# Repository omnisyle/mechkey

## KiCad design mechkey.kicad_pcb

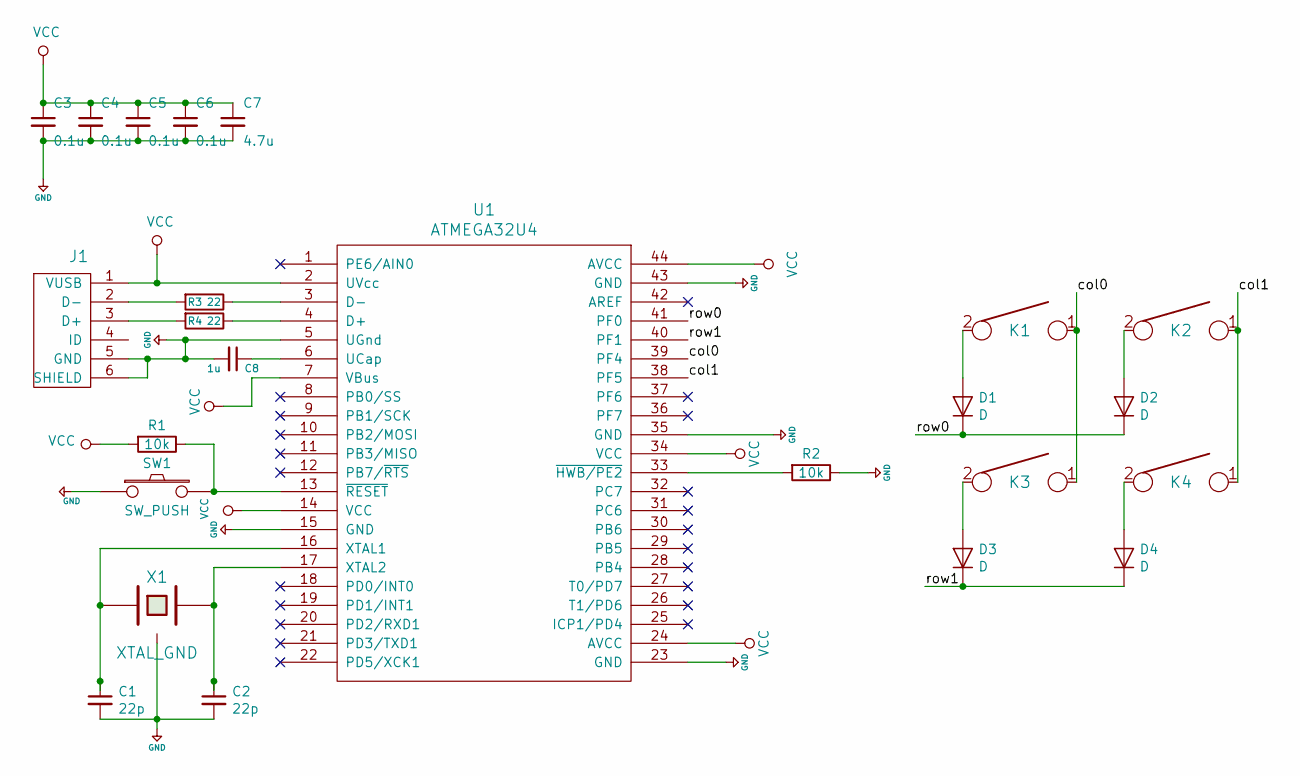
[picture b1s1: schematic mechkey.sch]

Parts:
C1, C2: 22p; C_0805_2012Metric_Pad1.15x1.40mm_HandSolder
C3, C4, C5, C6: 0.1u; C_0805_2012Metric_Pad1.15x1.40mm_HandSolder
C7: 4.7u; C_0805_2012Metric_Pad1.15x1.40mm_HandSolder
C8: 1u; C_0805_2012Metric_Pad1.15x1.40mm_HandSolder
D1, D2, D3, D4: D; D_axial
J1: USB_mini_micro_B; USB_miniB_hirose_5S8
K1, K2, K3, K4: KEYSW; Mx_Alps_100
R1, R2: 10k; R_0805_2012Metric_Pad1.15x1.40mm_HandSolder
R3, R4: 22; R_0805_2012Metric_Pad1.15x1.40mm_HandSolder
SW1: SW_PUSH; SW_SPST_TL3342
U1: ATMEGA32U4; TQFP-44_10x10mm_P0.8mm
X1: XTAL_GND; Crystal_SMD_SeikoEpson_FA238-4Pin_3.2x2.5mm_HandSoldering

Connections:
+5V: C1.2, C2.2, C3.2, C4.2, C5.2, C6.2, C7.2, C8.2, J1.5 (GND), J1.6 (SHIELD), R2.1, SW1.1, U1.5 (UGnd), U1.15 (GND), U1.23 (GND), U1.35 (GND), U1.43 (GND), X1.3
/col0: K1.1, K3.1, U1.39 (PF4)
/col1: K2.1, K4.1, U1.38 (PF5)
/row0: D1.1 (K), D2.1 (K), U1.41 (PF0)
/row1: D3.1 (K), D4.1 (K), U1.40 (PF1)
unnamed: C1.1, U1.16 (XTAL1), X1.1
unnamed: C2.1, U1.17 (XTAL2), X1.2
unnamed: C8.1, U1.6 (UCap)
unnamed: D1.2 (A), K1.2
unnamed: D2.2 (A), K2.2
unnamed: D3.2 (A), K3.2
unnamed: D4.2 (A), K4.2
unnamed: J1.2 (D-), R3.2
unnamed: J1.3 (D+), R4.2
unnamed: R1.1, SW1.2, U1.13 (~RESET)
unnamed: R2.2, U1.33 (~HWB/PE2)
unnamed: R3.1, U1.3 (D-)
unnamed: R4.1, U1.4 (D+)
VCC: C3.1, C4.1, C5.1, C6.1, C7.1, J1.1 (VUSB), R1.2, U1.2 (UVcc), U1.7 (VBus), U1.14 (VCC), U1.24 (AVCC), U1.34 (VCC), U1.44 (AVCC)

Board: 2 copper layers, 24 parts (0 on the bottom side), 19 nets, no tracks yet.
